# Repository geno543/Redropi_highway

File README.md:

# Radropi - Asteroid and Meteor Detection System

## Project Description

the project aims to detect asteroids and meteor movement using high-quality cameras and radar detection methods using an AI model for accurate analysis, and it classifies bodies be in three categories: non-meteor, meteor, and asteroid. It also has software for detecting the shape and size of meteors.It consists of two systems: a solar power monitoring system and an asteroid monitoring system.

### Classification Categories

The AI model classifies detected objects into three categories:
- **Non-meteor**: Background objects, aircraft, satellites
- **Meteor**: Burning debris entering Earth's atmosphere
- **Asteroid**: Larger rocky bodies in space

## Hardware Components

### Main Processing Unit
- Raspberry Pi 5 (4GB) - High-performance computing platform

### Detection Equipment
- IMX462 Starvis All-Sky Camera - Outstanding low-light performance
- Compact Automatic Satellite Dish - Auto-tracking capabilities
- Ublox NEO-6M GPS Module - Precise positioning

### Mechanical Components
- 4x MG995 Servo Motors - Robust tracking mechanisms
- Light Dependent Resistors (LDR) - Environmental sensing

## Project Images

### 3D Model

*Complete 3D model showing all components integrated*

### PCB Design

*Custom Raspberry Pi HAT for sensor integration*

## Bill of Materials

| Item | Quantity | Description | Unit Price (USD) | Purchase Link |
|------|----------|-------------|------------------|---------------|
| Raspberry Pi 5 (16GB) | 1 | Latest flagship board with high performance | $120 | [Raspberry Pi Foundation](https://www.raspberrypi.com/products/raspberry-pi-5/) |
| IMX462 Starvis All-Sky Cam | 1 | Outstanding low-light astrophotography camera | $40.18 | [AliExpress](https://ar.aliexpress.com/item/1005008679477184.html?spm=a2g0o.productlist.main.1.456alOpKlOpKBb&algo_pvid=c9047dc4-e725-4e11-98f2-fbd365b288b9&algo_exp_id=c9047dc4-e725-4e11-98f2-fbd365b288b9-0&pdp_ext_f=%7B%22order%22%3A%2211%22%2C%22eval%22%3A%221%22%7D&pdp_npi=4%40dis%21EGP%211766.78%211713.78%21%21%2133.00%2132.01%21%40212e508d17540195159431204eb48c%2112000046209347055%21sea%21EG%216183184762%21ABX&curPageLogUid=M117VafgYumd&utparam-url=scene%3Asearch%7Cquery_from%3A) |
| Compact Automatic Satellite Dish | 1 | Small, vehicle-friendly auto-tracking dish | $130 | [Alibaba](https://www.alibaba.com/showroom/auto-satellite-dish.html) |
| Ublox NEO-6M GPS Module | 1 | Popular hobby GPS with stable performance | $9.26 | [Most elec](9.26) |
| MG995 Servo Motor (Full metal gear) | 4 | Robust, high-torque servos | $15.94 | [Most elec](https://mostelectronic.com/shop/motors-drives-2/servo-motors-motors-drives-2/servo-motor-mg995-360-degree-metal-gear/) |
| LDR (Light Dependent Resistor, pack) | 1 | Standard 5mm LDRs (10-pack) | $4 | [Most elec](https://mostelectronic.com/shop/components/resistors-potentiometers/ldrs/photo-resistor-sensor-ldr-10mm/) |
| Project wiring kit | 5 | Assorted wires, jumper packs, tools | $7 | [Most elec](https://mostelectronic.com/shop/wires-crocodiles/u-shape-shield-breadboard-jumper-wires-140pcs/) |
|PCB from jlcpcb| 5 |The PCB hat for the pi | $11 |  JLCPCB |
**Total Estimated Cost: $325**

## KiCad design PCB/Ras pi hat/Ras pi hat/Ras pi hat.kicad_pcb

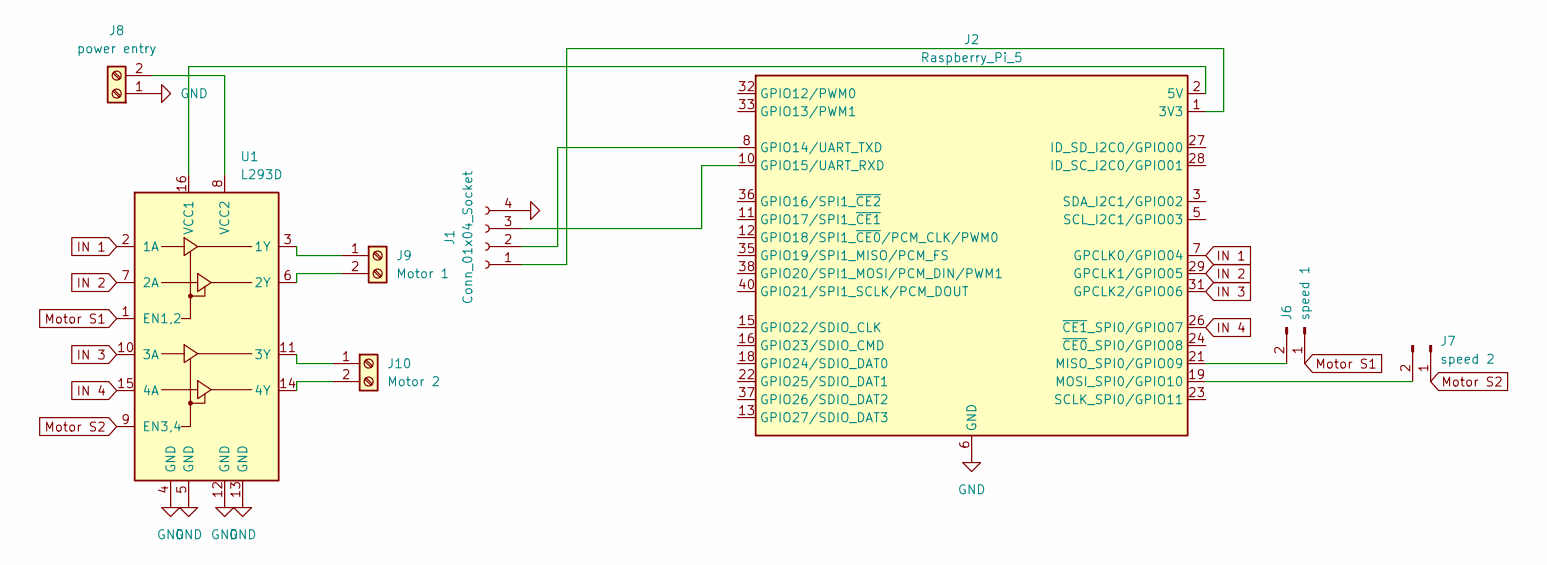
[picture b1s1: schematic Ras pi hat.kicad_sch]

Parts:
J1: Conn_01x04_Socket; PinSocket_1x04_P2.54mm_Vertical
J2: Raspberry_Pi_5; PinSocket_2x20_P2.54mm_Vertical
J6: speed 1; PinHeader_1x02_P2.54mm_Vertical
J7: speed 2; PinHeader_1x02_P2.54mm_Vertical
J8: power entry; TerminalBlock_MetzConnect_Type073_RT02602HBLU_1x02_P5.08mm_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
J9: Motor 1; TerminalBlock_MetzConnect_Type073_RT02602HBLU_1x02_P5.08mm_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
J10: Motor 2; TerminalBlock_MetzConnect_Type073_RT02602HBLU_1x02_P5.08mm_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
U1: L293D; DIP-16_W7.62mm

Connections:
GND: J1.4, J2.6 (GND), J2.9 (GND), J2.14 (GND), J2.20 (GND), J2.25 (GND), J2.30 (GND), J2.34 (GND), J2.39 (GND), J8.1, U1.4 (GND), U1.5 (GND), U1.12 (GND), U1.13 (GND)
IN 1: J2.7 (GPCLK0/GPIO04), U1.2 (1A)
IN 2: J2.29 (GPCLK1/GPIO05), U1.7 (2A)
IN 3: J2.31 (GPCLK2/GPIO06), U1.10 (3A)
IN 4: J2.26 (~CE1_SPI0/GPIO07), U1.15 (4A)
Motor S1: J6.1, U1.1 (EN1,2)
Motor S2: J7.1, U1.9 (EN3,4)
unnamed: J1.1, J2.1 (3V3), J2.17 (3V3)
unnamed: J1.2, J2.8 (GPIO14/UART_TXD)
unnamed: J1.3, J2.10 (GPIO15/UART_RXD)
unnamed: J2.21 (MISO_SPI0/GPIO09), J6.2
unnamed: J2.19 (MOSI_SPI0/GPIO10), J7.2
unnamed: J8.2, U1.8 (VCC2)
unnamed: J9.1, U1.3 (1Y)
unnamed: J9.2, U1.6 (2Y)
unnamed: J10.1, U1.11 (3Y)
unnamed: J10.2, U1.14 (4Y)
unnamed: J2.2 (5V), J2.4 (5V), U1.16 (VCC1)

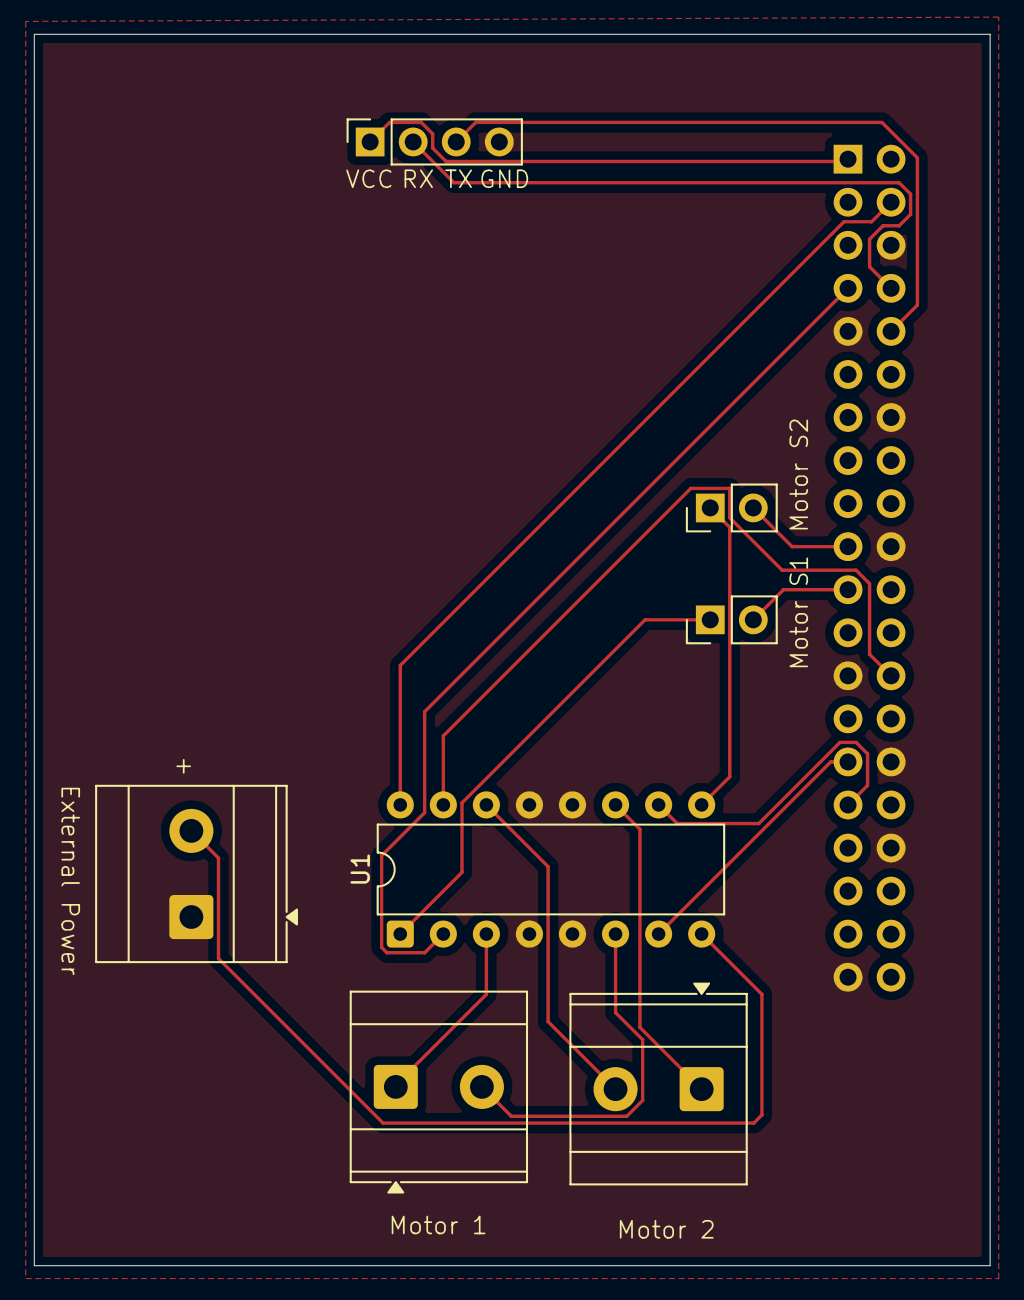
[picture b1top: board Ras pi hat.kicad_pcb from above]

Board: 2 copper layers, 56.4 x 72.6 mm, 8 parts (1 on the bottom side), 18 nets.

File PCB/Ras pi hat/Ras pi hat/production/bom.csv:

Designator,Footprint,Quantity,Value,LCSC Part #
J1,PinSocket_1x04_P2.54mm_Vertical,1,Conn_01x04_Socket,
J10,TerminalBlock_MetzConnect_Type073_RT02602HBLU_1x02_P5.08mm_Horizontal,1,Motor 2,
J2,PinSocket_2x20_P2.54mm_Vertical,1,Raspberry_Pi_4,
J6,PinHeader_1x02_P2.54mm_Vertical,1,speed 1,
J7,PinHeader_1x02_P2.54mm_Vertical,1,speed 2,
J8,TerminalBlock_MetzConnect_Type073_RT02602HBLU_1x02_P5.08mm_Horizontal,1,power entry,
J9,TerminalBlock_MetzConnect_Type073_RT02602HBLU_1x02_P5.08mm_Horizontal,1,Motor 1,
U1,DIP-16_W7.62mm,1,L293D,

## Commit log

2025-08-01 Initial commit: Complete Radropi asteroid detection system with firmware, PCB, 3D design, and documentation
